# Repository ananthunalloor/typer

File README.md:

# Project Typer - An ergonomic split keyboard with KMK firmware, using the Waveshare RP2040 Zero and a 3D-printed case based on the ErgoDox EZ.

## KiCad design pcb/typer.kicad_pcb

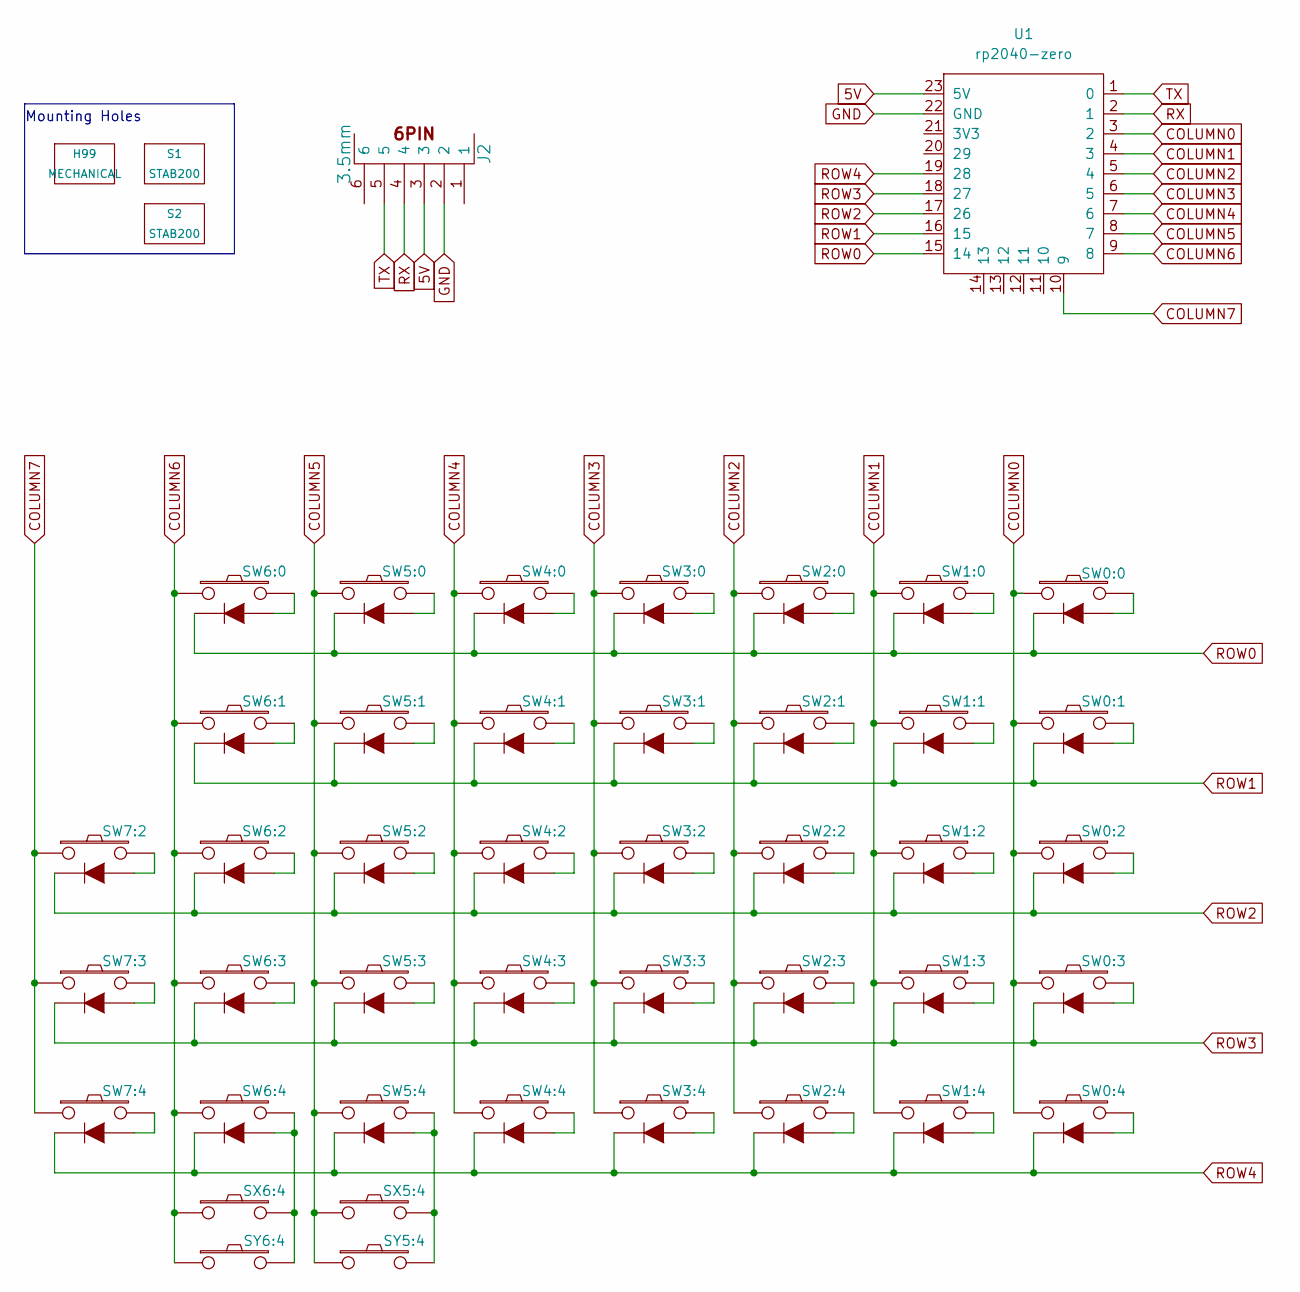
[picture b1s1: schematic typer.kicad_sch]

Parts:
H99: MECHANICAL; ErgoDOXmech
J2: 3.5mm; 4pin35mmAudio
S1, S2: STAB200; STAB_PCB940
SW0:0: SW0:0; MX_FLIP_XX
SW0:1: SW0:1; MX_FLIP_XX
SW0:2: SW0:2; MX_FLIP_XX
SW0:3: SW0:3; MX_FLIP_XX
SW0:4: SW0:4; MX_FLIP_DIODE
SW1:0: SW1:0; MX_FLIP_DIODE
SW1:1: SW1:1; MX_FLIP_DIODE
SW1:2: SW1:2; MX_FLIP_DIODE
SW1:3: SW1:3; MX_FLIP_DIODE
SW1:4: SW1:4; MX_FLIP_DIODE
SW2:0: SW2:0; MX_FLIP_DIODE
SW2:1: SW2:1; MX_FLIP_DIODE
SW2:2: SW2:2; MX_FLIP_DIODE
SW2:3: SW2:3; MX_FLIP_DIODE
SW2:4: SW2:4; MX_FLIP_DIODE
SW3:0: SW3:0; MX_FLIP_DIODE
SW3:1: SW3:1; MX_FLIP_DIODE
SW3:2: SW3:2; MX_FLIP_DIODE
SW3:3: SW3:3; MX_FLIP_DIODE
SW3:4: SW3:4; MX_FLIP_DIODE
SW4:0: SW4:0; MX_FLIP_DIODE
SW4:1: SW4:1; MX_FLIP_DIODE
SW4:2: SW4:2; MX_FLIP_DIODE
SW4:3: SW4:3; MX_FLIP_DIODE
SW4:4: SW4:4; MX_FLIP_DIODE
SW5:0: SW5:0; MX_FLIP_DIODE
SW5:1: SW5:1; MX_FLIP_DIODE
SW5:2: SW5:2; MX_FLIP_DIODE
SW5:3: SW5:3; MX_FLIP_DIODE
SW5:4: SW5:4; MX_FLIP_DIODE
SW6:0: SW6:0; MX_FLIP_DIODE
SW6:1: SW6:1; MX_FLIP_DIODE
SW6:2: SW6:2; MX_FLIP_DIODE
SW6:3: SW6:3; MX_FLIP_DIODE
SW6:4: SW6:4; MX_FLIP_DIODE
SW7:2: SW7:2; MX_FLIP_DIODE
SW7:3: SW7:3; MX_FLIP_DIODE
SW7:4: SW7:4; MX_FLIP_DIODE
SX5:4: SX5:4; MX_FLIP
SX6:4: SX6:4; MX_FLIP
SY5:4: SY5:4; MX_FLIP
SY6:4: SY6:4; MX_FLIP
U1: rp2040-zero; rp2040-zero-tht

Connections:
5V: J2.3, U1.23 (5V)
COLUMN0: SW0:0.1, SW0:1.1, SW0:2.1, SW0:3.1, SW0:4.1, U1.3 (2)
COLUMN1: SW1:0.1, SW1:1.1, SW1:2.1, SW1:3.1, SW1:4.1, U1.4 (3)
COLUMN2: SW2:0.1, SW2:1.1, SW2:2.1, SW2:3.1, SW2:4.1, U1.5 (4)
COLUMN3: SW3:0.1, SW3:1.1, SW3:2.1, SW3:3.1, SW3:4.1, U1.6 (5)
COLUMN4: SW4:0.1, SW4:1.1, SW4:2.1, SW4:3.1, SW4:4.1, U1.7 (6)
COLUMN5: SW5:0.1, SW5:1.1, SW5:2.1, SW5:3.1, SW5:4.1, SX5:4.1, SY5:4.1, U1.8 (7)
COLUMN6: SW6:0.1, SW6:1.1, SW6:2.1, SW6:3.1, SW6:4.1, SX6:4.1, SY6:4.1, U1.9 (8)
COLUMN7: SW7:2.1, SW7:3.1, SW7:4.1, U1.10 (9)
GND: J2.2, U1.22 (GND)
unnamed: SW0:0.2, SW0:0.3 (A)
unnamed: SW0:1.2, SW0:1.3 (A)
unnamed: SW0:2.2, SW0:2.3 (A)
unnamed: SW0:3.2, SW0:3.3 (A)
unnamed: SW0:4.2, SW0:4.3 (A)
unnamed: SW1:0.2, SW1:0.3 (A)
unnamed: SW1:1.2, SW1:1.3 (A)
unnamed: SW1:2.2, SW1:2.3 (A)
unnamed: SW1:3.2, SW1:3.3 (A)
unnamed: SW1:4.2, SW1:4.3 (A)
unnamed: SW2:0.2, SW2:0.3 (A)
unnamed: SW2:1.2, SW2:1.3 (A)
unnamed: SW2:2.2, SW2:2.3 (A)
unnamed: SW2:3.2, SW2:3.3 (A)
unnamed: SW2:4.2, SW2:4.3 (A)
unnamed: SW3:0.2, SW3:0.3 (A)
unnamed: SW3:1.2, SW3:1.3 (A)
unnamed: SW3:2.2, SW3:2.3 (A)
unnamed: SW3:3.2, SW3:3.3 (A)
unnamed: SW3:4.2, SW3:4.3 (A)
unnamed: SW4:0.2, SW4:0.3 (A)
unnamed: SW4:1.2, SW4:1.3 (A)
unnamed: SW4:2.2, SW4:2.3 (A)
unnamed: SW4:3.2, SW4:3.3 (A)
unnamed: SW4:4.2, SW4:4.3 (A)
unnamed: SW5:0.2, SW5:0.3 (A)
unnamed: SW5:1.2, SW5:1.3 (A)
unnamed: SW5:2.2, SW5:2.3 (A)
unnamed: SW5:3.2, SW5:3.3 (A)
unnamed: SW5:4.2, SW5:4.3 (A), SX5:4.2, SY5:4.2
unnamed: SW6:0.2, SW6:0.3 (A)
unnamed: SW6:1.2, SW6:1.3 (A)
unnamed: SW6:2.2, SW6:2.3 (A)
unnamed: SW6:3.2, SW6:3.3 (A)
unnamed: SW6:4.2, SW6:4.3 (A), SX6:4.2, SY6:4.2
unnamed: SW7:2.2, SW7:2.3 (A)
unnamed: SW7:3.2, SW7:3.3 (A)
unnamed: SW7:4.2, SW7:4.3 (A)
ROW0: SW0:0.4 (K), SW1:0.4 (K), SW2:0.4 (K), SW3:0.4 (K), SW4:0.4 (K), SW5:0.4 (K), SW6:0.4 (K), U1.15 (14)
ROW1: SW0:1.4 (K), SW1:1.4 (K), SW2:1.4 (K), SW3:1.4 (K), SW4:1.4 (K), SW5:1.4 (K), SW6:1.4 (K), U1.16 (15)
ROW2: SW0:2.4 (K), SW1:2.4 (K), SW2:2.4 (K), SW3:2.4 (K), SW4:2.4 (K), SW5:2.4 (K), SW6:2.4 (K), SW7:2.4 (K), U1.17 (26)
ROW3: SW0:3.4 (K), SW1:3.4 (K), SW2:3.4 (K), SW3:3.4 (K), SW4:3.4 (K), SW5:3.4 (K), SW6:3.4 (K), SW7:3.4 (K), U1.18 (27)
ROW4: SW0:4.4 (K), SW1:4.4 (K), SW2:4.4 (K), SW3:4.4 (K), SW4:4.4 (K), SW5:4.4 (K), SW6:4.4 (K), SW7:4.4 (K), U1.19 (28)
RX: J2.4, U1.2 (1)
TX: J2.5, U1.1 (0)

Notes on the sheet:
Mounting Holes

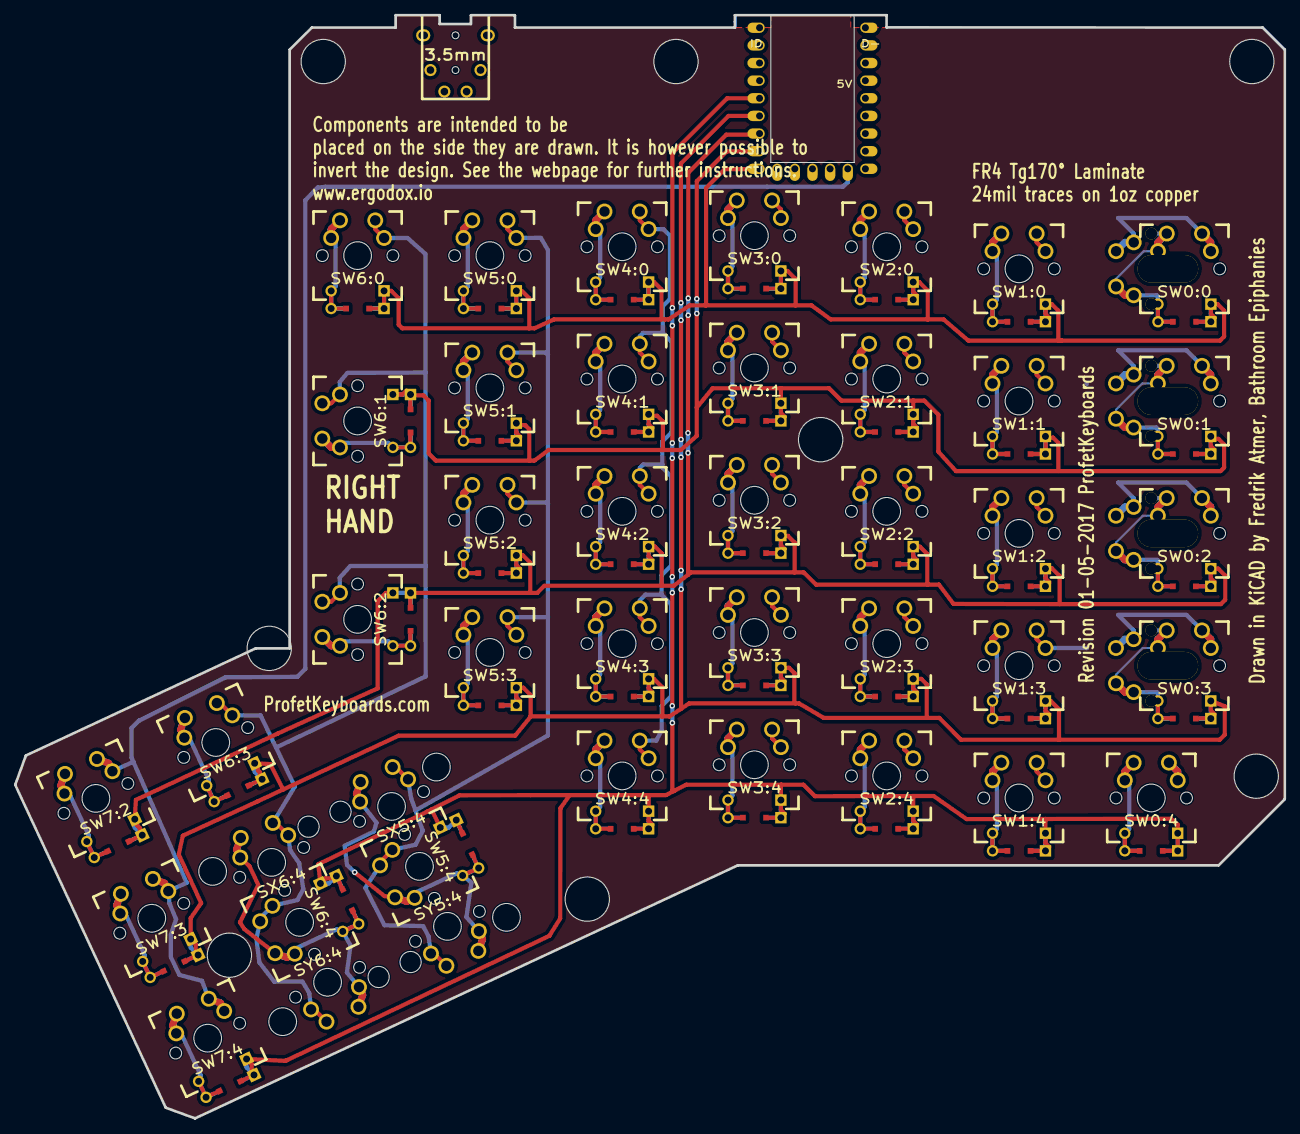
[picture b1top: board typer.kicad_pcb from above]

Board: 2 copper layers, 182.8 x 158.9 mm, 47 parts (0 on the bottom side), 55 nets.

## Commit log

2023-11-25 readme basic code
2023-11-26 coord mapping
2023-11-27 working layers
2023-11-27 final changes
2023-11-27 layer changes
2023-11-27 lint
2023-11-28 pcb design base commit
2023-11-28 lib change
2023-11-29 new project updates
2023-11-29 placement update
2023-11-30 start track layout
2023-11-30 row track layout added
2023-12-01 column traces
2023-12-01 lib changes removed col tacres
2023-12-01 row connected
2023-12-01 traces added
2023-12-01 added holes
2023-12-01 holes done
